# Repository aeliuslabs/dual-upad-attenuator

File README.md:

# dual-upad-attenuator
Dual Channel U-Pad Attenuator PCB

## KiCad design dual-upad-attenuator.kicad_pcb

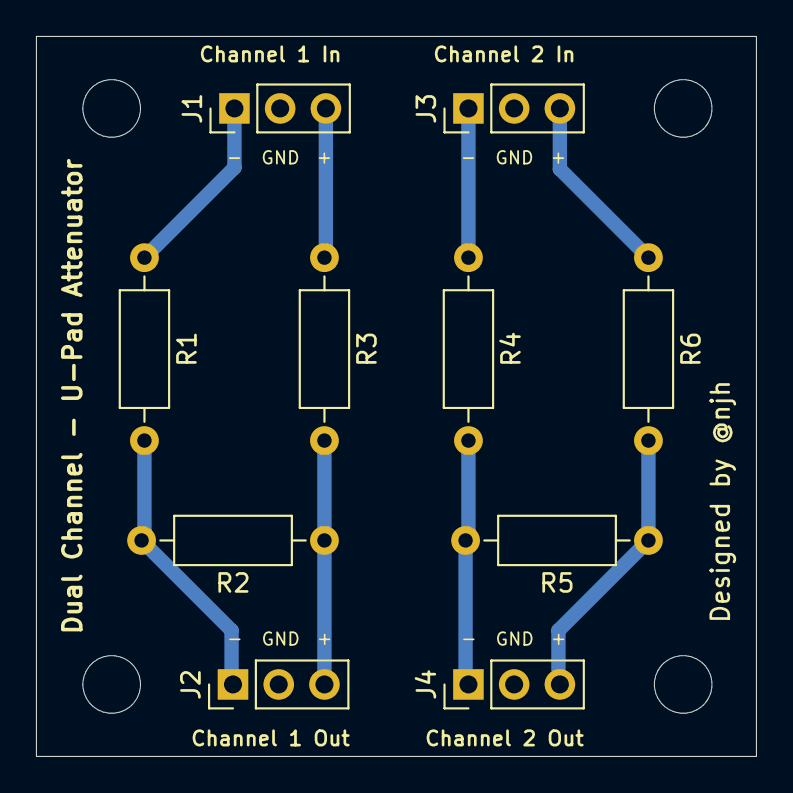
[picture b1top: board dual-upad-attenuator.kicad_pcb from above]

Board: 2 copper layers, 40.0 x 40.0 mm, 10 parts (0 on the bottom side), 9 nets.

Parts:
J1, J2, J3, J4: Conn_01x03_Male; PinHeader_1x03_P2.54mm_Vertical
R1, R2, R3, R4, R5, R6: R; R_Axial_DIN0207_L6.3mm_D2.5mm_P10.16mm_Horizontal

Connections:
GND: J1.2, J2.2, J3.2, J4.2
unnamed: J1.1, R1.1
unnamed: J1.3, R3.1
unnamed: J2.1, R1.2, R2.2
unnamed: J2.3, R2.1, R3.2
unnamed: J3.1, R4.1
unnamed: J3.3, R6.1
unnamed: J4.1, R4.2, R5.2
unnamed: J4.3, R5.1, R6.2

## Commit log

2020-10-23 Added KiCad files - Project - Schematic - PCB layout
2020-10-23 Ignore the generated gerber files
